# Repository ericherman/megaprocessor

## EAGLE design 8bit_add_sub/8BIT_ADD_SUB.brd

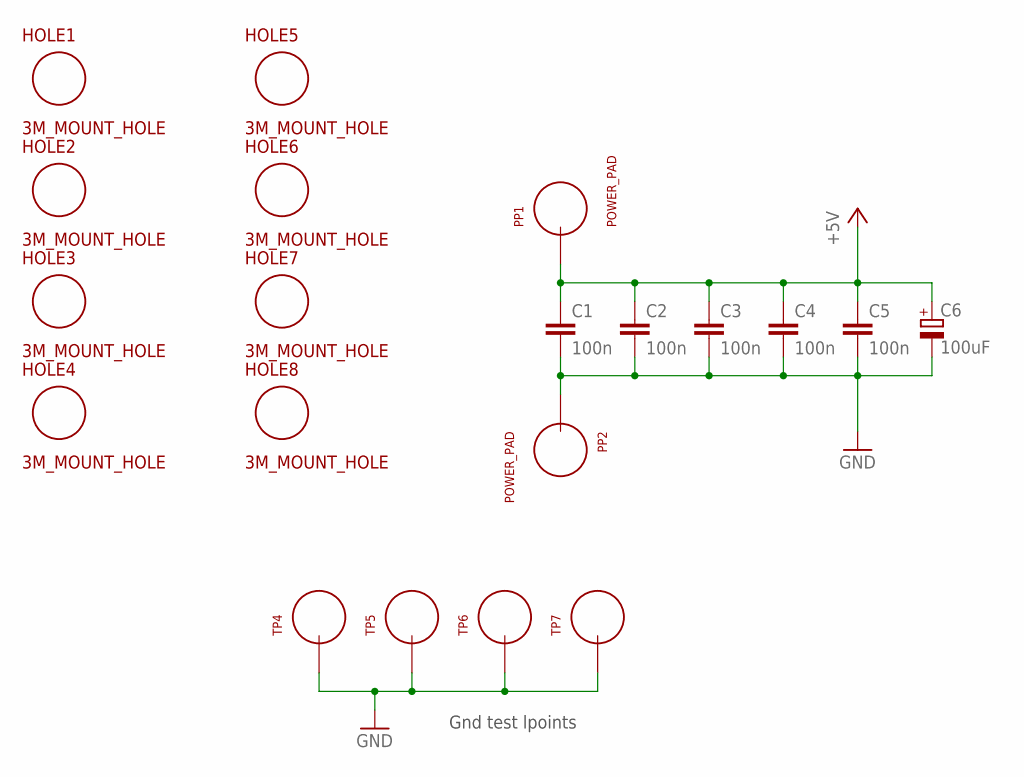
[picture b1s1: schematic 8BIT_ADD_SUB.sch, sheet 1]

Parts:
C1, C2, C3, C4, C5: 100n; CAP_P2INCH
C6: 100uF; POLARISED_CAP_2P5
HOLE1, HOLE2, HOLE3, HOLE4, HOLE5, HOLE6, HOLE7, HOLE8: 3M_MOUNT_HOLE; 3M_HOLE
PP1, PP2: POWER_PAD
TP4, TP5, TP6, TP7: TEST_LOOP

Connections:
+5V: C1.1, C2.1, C3.1, C4.1, C5.1, C6.A, PP1.1; also elsewhere on the board
GND: C1.2, C2.2, C3.2, C4.2, C5.2, C6.K, PP2.1, TP4.P$1, TP5.P$1, TP6.P$1, TP7.P$1; also elsewhere on the board

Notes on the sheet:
Gnd test lpoints

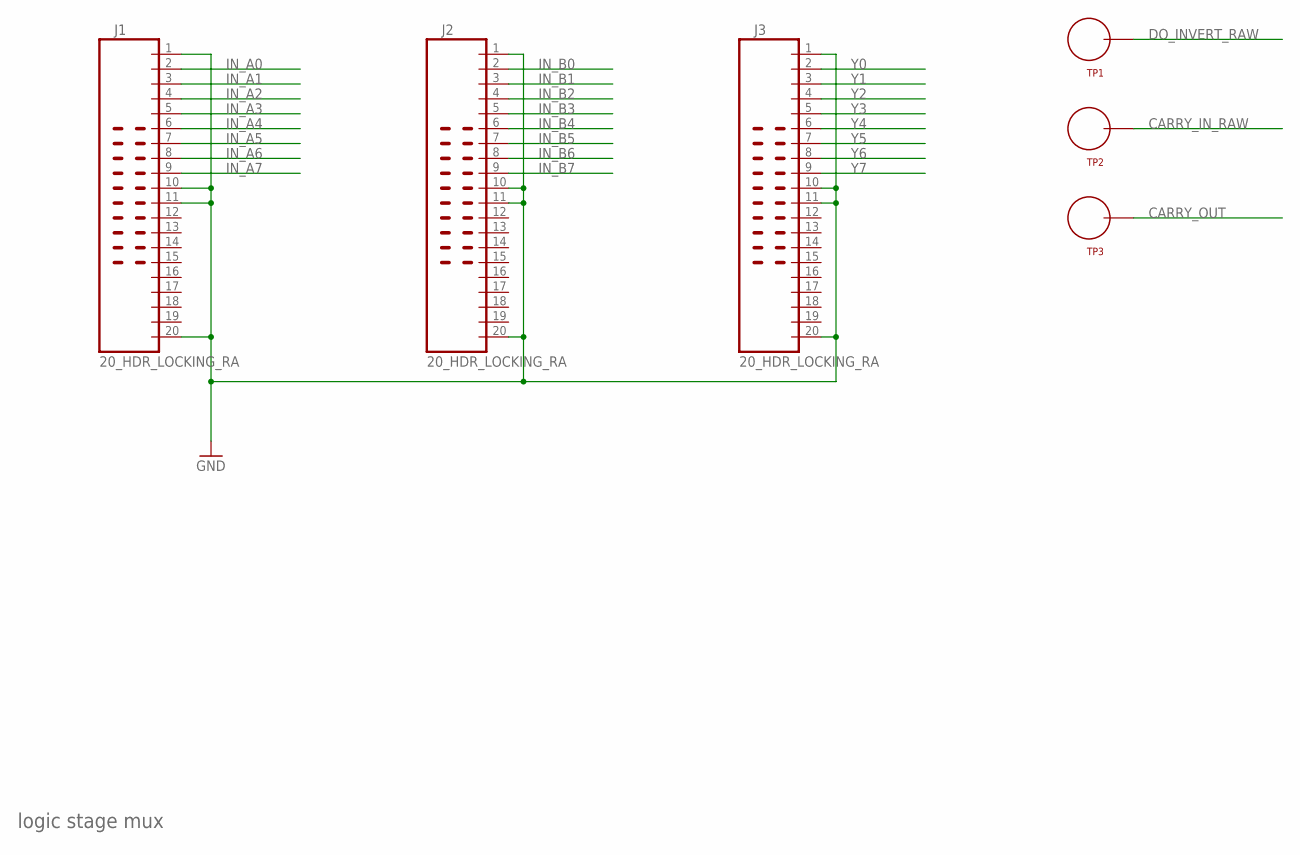
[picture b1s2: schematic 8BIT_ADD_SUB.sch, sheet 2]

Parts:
J1, J2, J3: 20_HDR_LOCKING_RA
TP1, TP2, TP3: TEST_LOOP

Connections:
CARRY_IN_RAW: TP2.P$1; also elsewhere on the board
CARRY_OUT: TP3.P$1; also elsewhere on the board
DO_INVERT_RAW: TP1.P$1; also elsewhere on the board
GND: J1.1, J1.10, J1.11, J1.20, J2.1, J2.10, J2.11, J2.20, J3.1, J3.10, J3.11, J3.20; also elsewhere on the board
IN_A0: J1.2; also elsewhere on the board
IN_A1: J1.3; also elsewhere on the board
IN_A2: J1.4; also elsewhere on the board
IN_A3: J1.5; also elsewhere on the board
IN_A4: J1.6; also elsewhere on the board
IN_A5: J1.7; also elsewhere on the board
IN_A6: J1.8; also elsewhere on the board
IN_A7: J1.9; also elsewhere on the board
IN_B0: J2.2; also elsewhere on the board
IN_B1: J2.3; also elsewhere on the board
IN_B2: J2.4; also elsewhere on the board
IN_B3: J2.5; also elsewhere on the board
IN_B4: J2.6; also elsewhere on the board
IN_B5: J2.7; also elsewhere on the board
IN_B6: J2.8; also elsewhere on the board
IN_B7: J2.9; also elsewhere on the board
Y0: J3.2; also elsewhere on the board
Y1: J3.3; also elsewhere on the board
Y2: J3.4; also elsewhere on the board
Y3: J3.5; also elsewhere on the board
Y4: J3.6; also elsewhere on the board
Y5: J3.7; also elsewhere on the board
Y6: J3.8; also elsewhere on the board
Y7: J3.9; also elsewhere on the board

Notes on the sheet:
logic stage mux

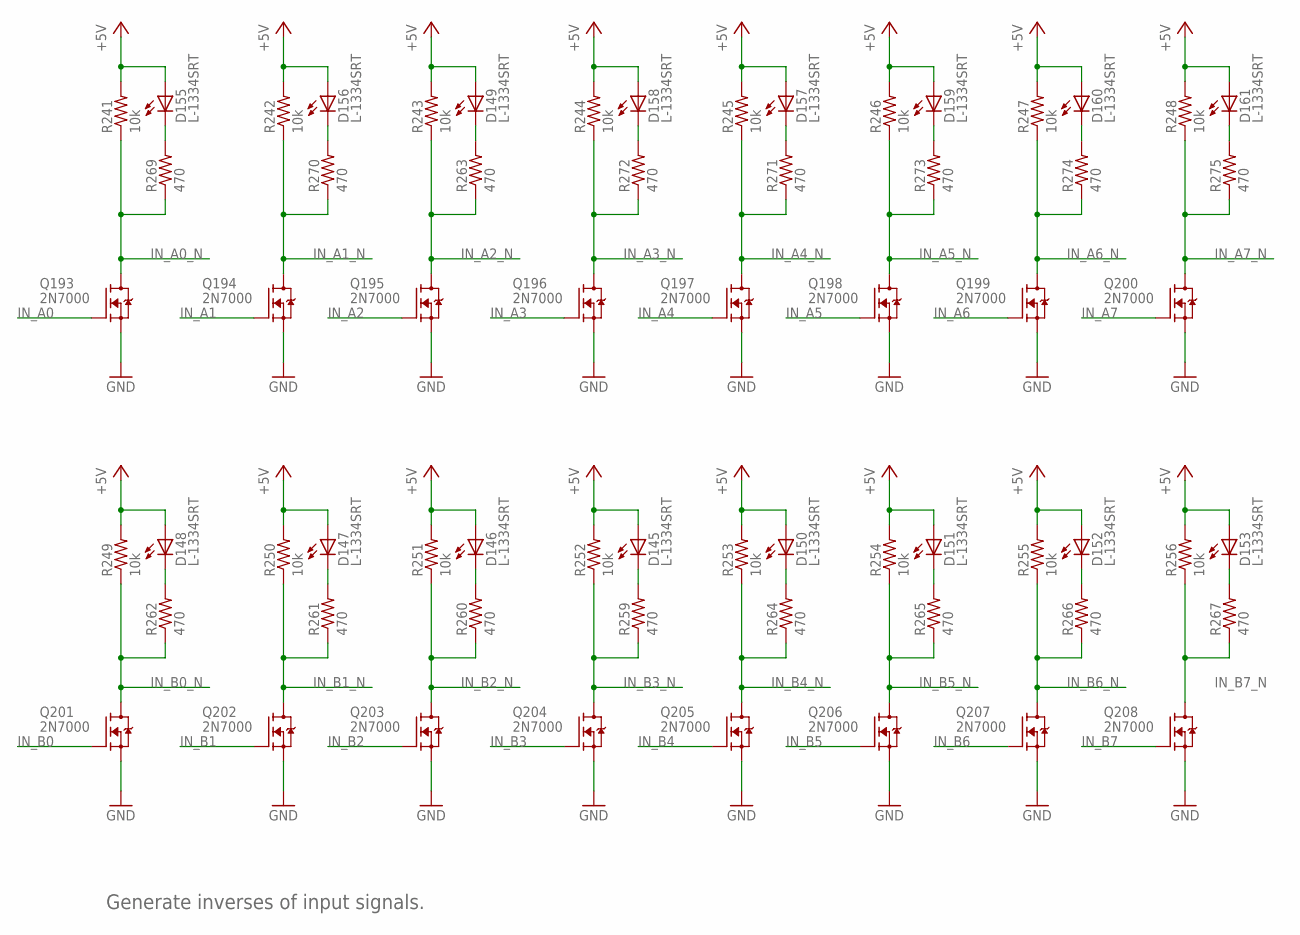
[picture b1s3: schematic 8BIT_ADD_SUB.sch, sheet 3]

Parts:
D145, D146, D147, D148, D149, D150, D151, D152, D153, D155, D156, D157, D158, D159, D160, D161: L-1334SRT; LED3MM
Q193, Q194, Q195, Q196, Q197, Q198, Q199, Q200, Q201, Q202, Q203, Q204, Q205, Q206, Q207, Q208: 2N7000; TO92-DGS
R241, R242, R243, R244, R245, R246, R247, R248, R249, R250, R251, R252, R253, R254, R255, R256: 10k; R_P2INCH
R259, R260, R261, R262, R263, R264, R265, R266, R267, R269, R270, R271, R272, R273, R274, R275: 470; R_P2INCH

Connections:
+5V: D145.A, D146.A, D147.A, D148.A, D149.A, D150.A, D151.A, D152.A, D153.A, D155.A, D156.A, D157.A, D158.A, D159.A, D160.A, D161.A, R241.2, R242.2, R243.2, R244.2, R245.2, R246.2, R247.2, R248.2, R249.2, R250.2, R251.2, R252.2, R253.2, R254.2, R255.2, R256.2; also elsewhere on the board
GND: Q193.S, Q194.S, Q195.S, Q196.S, Q197.S, Q198.S, Q199.S, Q200.S, Q201.S, Q202.S, Q203.S, Q204.S, Q205.S, Q206.S, Q207.S, Q208.S; also elsewhere on the board
IN_A0: Q193.G; also elsewhere on the board
IN_A0_N: Q193.D, R241.1, R269.1; also elsewhere on the board
IN_A1: Q194.G; also elsewhere on the board
IN_A1_N: Q194.D, R242.1, R270.1; also elsewhere on the board
IN_A2: Q195.G; also elsewhere on the board
IN_A2_N: Q195.D, R243.1, R263.1; also elsewhere on the board
IN_A3: Q196.G; also elsewhere on the board
IN_A3_N: Q196.D, R244.1, R272.1; also elsewhere on the board
IN_A4: Q197.G; also elsewhere on the board
IN_A4_N: Q197.D, R245.1, R271.1; also elsewhere on the board
IN_A5: Q198.G; also elsewhere on the board
IN_A5_N: Q198.D, R246.1, R273.1; also elsewhere on the board
IN_A6: Q199.G; also elsewhere on the board
IN_A6_N: Q199.D, R247.1, R274.1; also elsewhere on the board
IN_A7: Q200.G; also elsewhere on the board
IN_A7_N: Q200.D, R248.1, R275.1; also elsewhere on the board
IN_B0: Q201.G; also elsewhere on the board
IN_B0_N: Q201.D, R249.1, R262.1; also elsewhere on the board
IN_B1: Q202.G; also elsewhere on the board
IN_B1_N: Q202.D, R250.1, R261.1; also elsewhere on the board
IN_B2: Q203.G; also elsewhere on the board
IN_B2_N: Q203.D, R251.1, R260.1; also elsewhere on the board
IN_B3: Q204.G; also elsewhere on the board
IN_B3_N: Q204.D, R252.1, R259.1; also elsewhere on the board
IN_B4: Q205.G; also elsewhere on the board
IN_B4_N: Q205.D, R253.1, R264.1; also elsewhere on the board
IN_B5: Q206.G; also elsewhere on the board
IN_B5_N: Q206.D, R254.1, R265.1; also elsewhere on the board
IN_B6: Q207.G; also elsewhere on the board
IN_B6_N: Q207.D, R255.1, R266.1; also elsewhere on the board
IN_B7: Q208.G; also elsewhere on the board
IN_B7_N: Q208.D, R256.1, R267.1; also elsewhere on the board
unnamed: D145.K (C), R259.2
unnamed: D146.K (C), R260.2
unnamed: D147.K (C), R261.2
unnamed: D148.K (C), R262.2
unnamed: D149.K (C), R263.2
unnamed: D150.K (C), R264.2
unnamed: D151.K (C), R265.2
unnamed: D152.K (C), R266.2
unnamed: D153.K (C), R267.2
unnamed: D155.K (C), R269.2
unnamed: D156.K (C), R270.2
unnamed: D157.K (C), R271.2
unnamed: D158.K (C), R272.2
unnamed: D159.K (C), R273.2
unnamed: D160.K (C), R274.2
unnamed: D161.K (C), R275.2

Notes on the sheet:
Generate inverses of input signals.

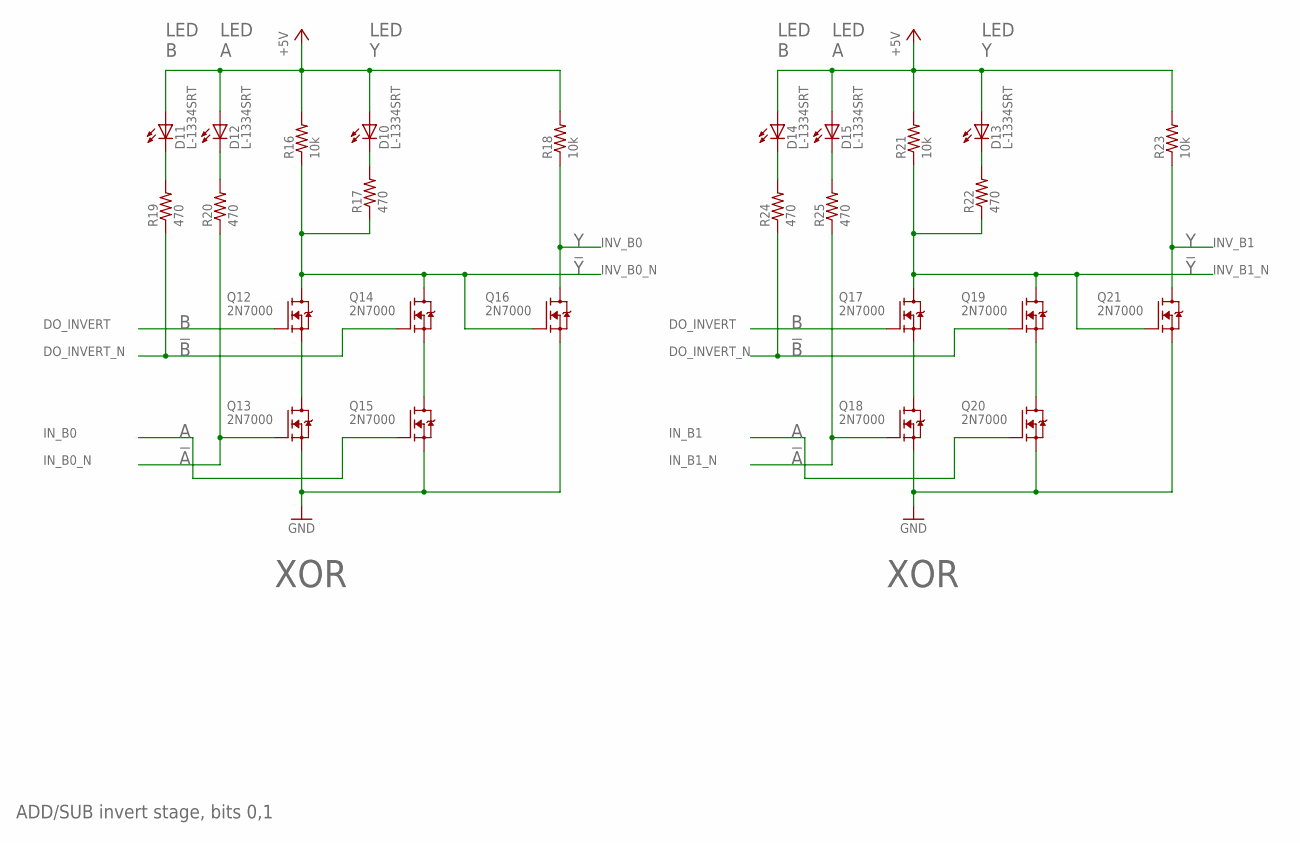
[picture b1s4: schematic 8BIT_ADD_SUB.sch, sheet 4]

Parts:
D10, D11, D12, D13, D14, D15: L-1334SRT; LED3MM
Q12, Q13, Q14, Q15, Q16, Q17, Q18, Q19, Q20, Q21: 2N7000; TO92-DGS
R16, R18, R21, R23: 10k; R_P2INCH
R17, R19, R20, R22, R24, R25: 470; R_P2INCH

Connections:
+5V: D10.A, D11.A, D12.A, D13.A, D14.A, D15.A, R16.2, R18.2, R21.2, R23.2; also elsewhere on the board
DO_INVERT: Q12.G, Q17.G; also elsewhere on the board
DO_INVERT_N: Q14.G, Q19.G, R19.1, R24.1; also elsewhere on the board
GND: Q13.S, Q15.S, Q16.S, Q18.S, Q20.S, Q21.S; also elsewhere on the board
INV_B0: Q16.D, R18.1; also elsewhere on the board
INV_B0_N: Q12.D, Q14.D, Q16.G, R16.1, R17.1; also elsewhere on the board
INV_B1: Q21.D, R23.1; also elsewhere on the board
INV_B1_N: Q17.D, Q19.D, Q21.G, R21.1, R22.1; also elsewhere on the board
IN_B0: Q15.G; also elsewhere on the board
IN_B0_N: Q13.G, R20.1; also elsewhere on the board
IN_B1: Q20.G; also elsewhere on the board
IN_B1_N: Q18.G, R25.1; also elsewhere on the board
unnamed: Q12.S, Q13.D
unnamed: Q14.S, Q15.D
unnamed: D10.K (C), R17.2
unnamed: D12.K (C), R20.2
unnamed: D11.K (C), R19.2
unnamed: Q17.S, Q18.D
unnamed: Q19.S, Q20.D
unnamed: D13.K (C), R22.2
unnamed: D15.K (C), R25.2
unnamed: D14.K (C), R24.2

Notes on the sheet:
ADD/SUB invert stage, bits 0,1
XOR
LED A
LED B
LED Y

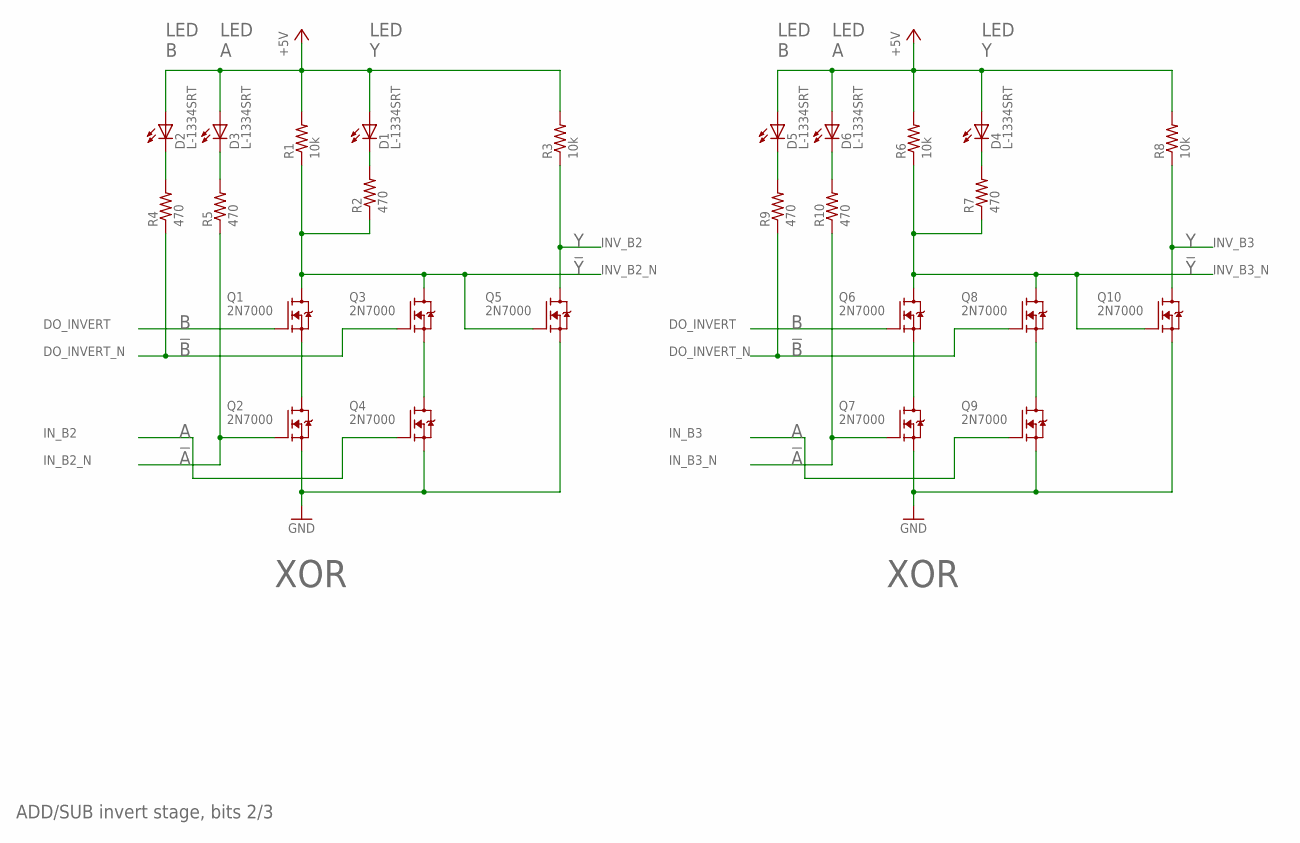
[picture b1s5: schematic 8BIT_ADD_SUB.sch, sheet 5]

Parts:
D1, D2, D3, D4, D5, D6: L-1334SRT; LED3MM
Q1, Q2, Q3, Q4, Q5, Q6, Q7, Q8, Q9, Q10: 2N7000; TO92-DGS
R1, R3, R6, R8: 10k; R_P2INCH
R2, R4, R5, R7, R9, R10: 470; R_P2INCH

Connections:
+5V: D1.A, D2.A, D3.A, D4.A, D5.A, D6.A, R1.2, R3.2, R6.2, R8.2; also elsewhere on the board
DO_INVERT: Q1.G, Q6.G; also elsewhere on the board
DO_INVERT_N: Q3.G, Q8.G, R4.1, R9.1; also elsewhere on the board
GND: Q2.S, Q4.S, Q5.S, Q7.S, Q9.S, Q10.S; also elsewhere on the board
INV_B2: Q5.D, R3.1; also elsewhere on the board
INV_B2_N: Q1.D, Q3.D, Q5.G, R1.1, R2.1; also elsewhere on the board
INV_B3: Q10.D, R8.1; also elsewhere on the board
INV_B3_N: Q6.D, Q8.D, Q10.G, R6.1, R7.1; also elsewhere on the board
IN_B2: Q4.G; also elsewhere on the board
IN_B2_N: Q2.G, R5.1; also elsewhere on the board
IN_B3: Q9.G; also elsewhere on the board
IN_B3_N: Q7.G, R10.1; also elsewhere on the board
unnamed: Q1.S, Q2.D
unnamed: Q3.S, Q4.D
unnamed: D1.K (C), R2.2
unnamed: D3.K (C), R5.2
unnamed: D2.K (C), R4.2
unnamed: Q6.S, Q7.D
unnamed: Q8.S, Q9.D
unnamed: D4.K (C), R7.2
unnamed: D6.K (C), R10.2
unnamed: D5.K (C), R9.2

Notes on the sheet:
ADD/SUB invert stage, bits 2/3
XOR
LED A
LED B
LED Y

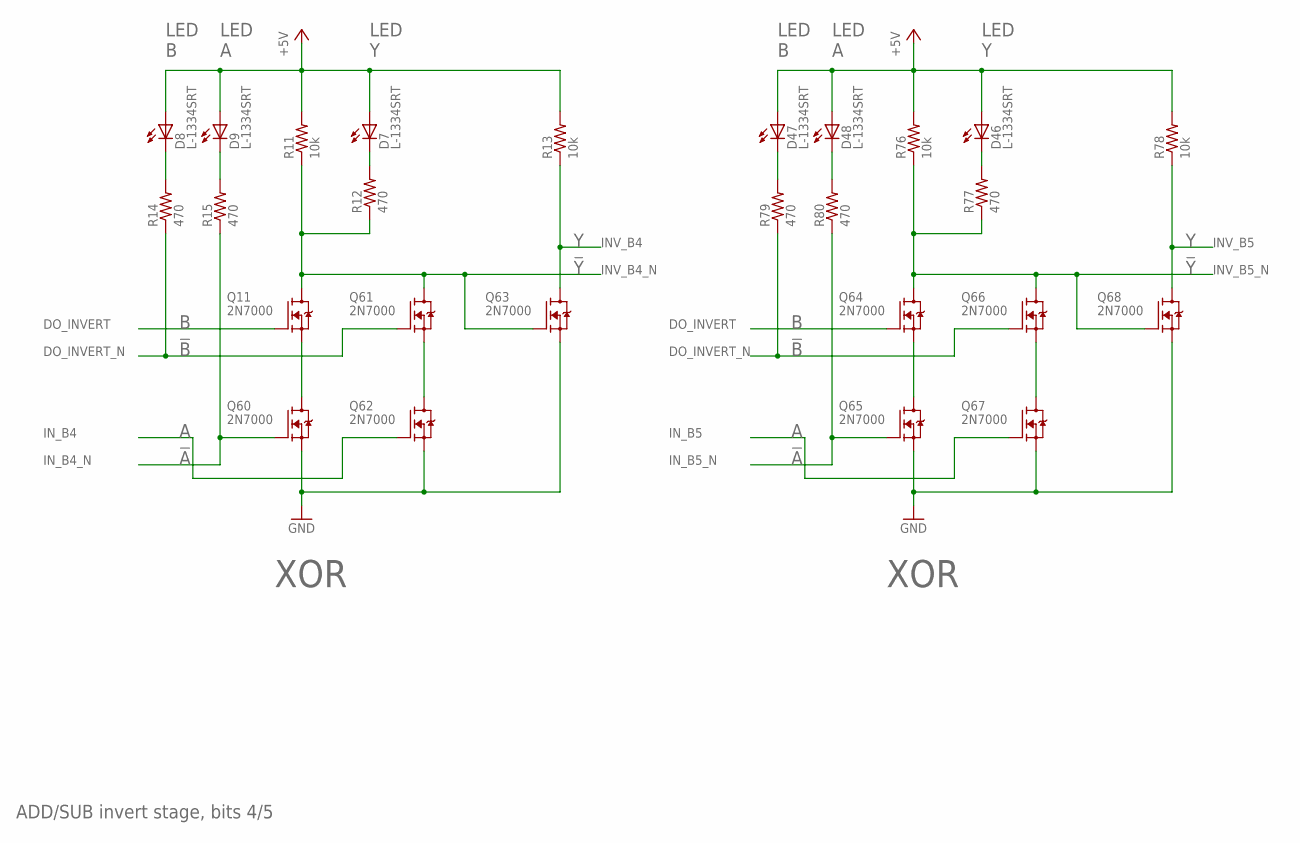
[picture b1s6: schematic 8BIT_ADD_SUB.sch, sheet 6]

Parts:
D7, D8, D9, D46, D47, D48: L-1334SRT; LED3MM
Q11, Q60, Q61, Q62, Q63, Q64, Q65, Q66, Q67, Q68: 2N7000; TO92-DGS
R11, R13, R76, R78: 10k; R_P2INCH
R12, R14, R15, R77, R79, R80: 470; R_P2INCH

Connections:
+5V: D7.A, D8.A, D9.A, D46.A, D47.A, D48.A, R11.2, R13.2, R76.2, R78.2; also elsewhere on the board
DO_INVERT: Q11.G, Q64.G; also elsewhere on the board
DO_INVERT_N: Q61.G, Q66.G, R14.1, R79.1; also elsewhere on the board
GND: Q60.S, Q62.S, Q63.S, Q65.S, Q67.S, Q68.S; also elsewhere on the board
INV_B4: Q63.D, R13.1; also elsewhere on the board
INV_B4_N: Q11.D, Q61.D, Q63.G, R11.1, R12.1; also elsewhere on the board
INV_B5: Q68.D, R78.1; also elsewhere on the board
INV_B5_N: Q64.D, Q66.D, Q68.G, R76.1, R77.1; also elsewhere on the board
IN_B4: Q62.G; also elsewhere on the board
IN_B4_N: Q60.G, R15.1; also elsewhere on the board
IN_B5: Q67.G; also elsewhere on the board
IN_B5_N: Q65.G, R80.1; also elsewhere on the board
unnamed: Q11.S, Q60.D
unnamed: Q61.S, Q62.D
unnamed: D7.K (C), R12.2
unnamed: D9.K (C), R15.2
unnamed: D8.K (C), R14.2
unnamed: Q64.S, Q65.D
unnamed: Q66.S, Q67.D
unnamed: D46.K (C), R77.2
unnamed: D48.K (C), R80.2
unnamed: D47.K (C), R79.2

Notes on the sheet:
ADD/SUB invert stage, bits 4/5
XOR
LED A
LED B
LED Y

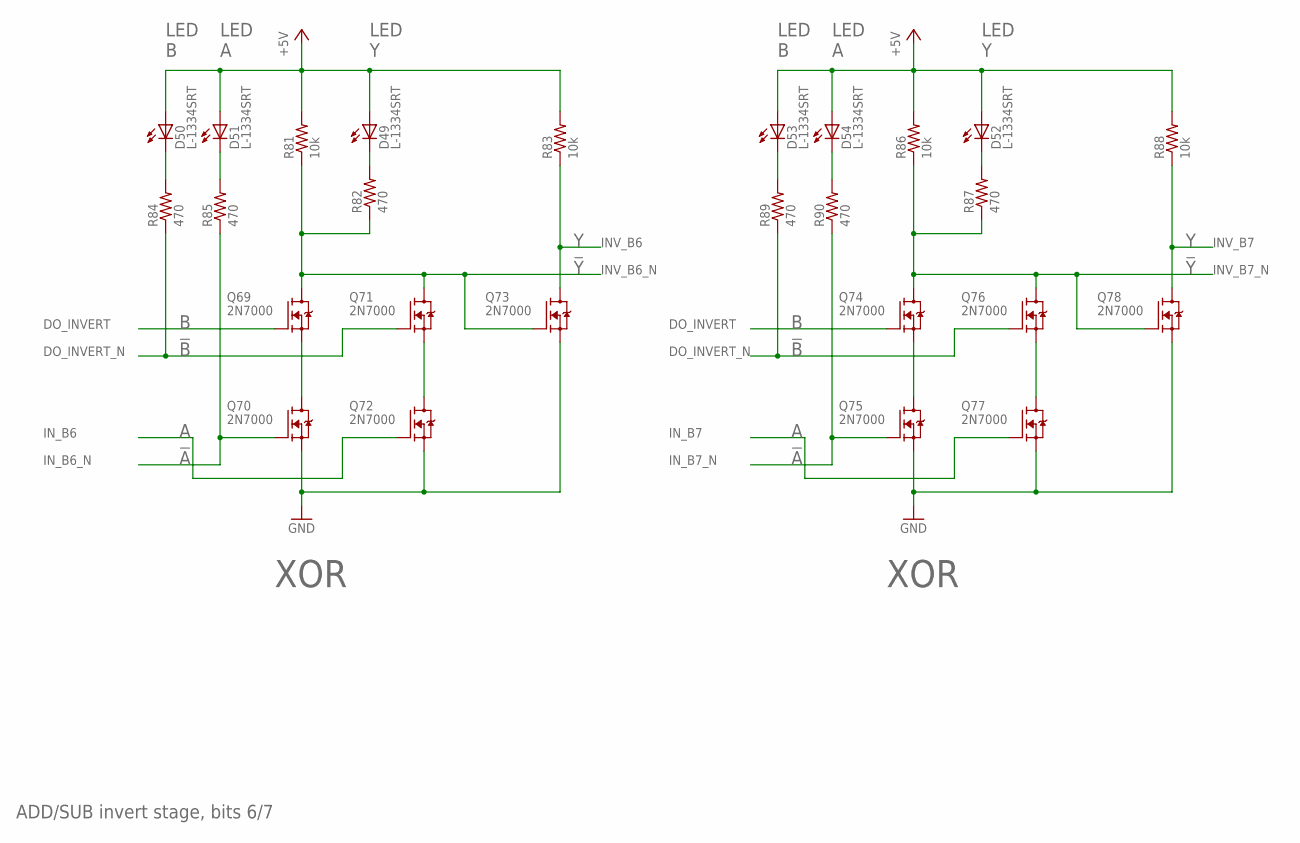
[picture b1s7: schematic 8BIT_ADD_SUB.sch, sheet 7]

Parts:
D49, D50, D51, D52, D53, D54: L-1334SRT; LED3MM
Q69, Q70, Q71, Q72, Q73, Q74, Q75, Q76, Q77, Q78: 2N7000; TO92-DGS
R81, R83, R86, R88: 10k; R_P2INCH
R82, R84, R85, R87, R89, R90: 470; R_P2INCH

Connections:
+5V: D49.A, D50.A, D51.A, D52.A, D53.A, D54.A, R81.2, R83.2, R86.2, R88.2; also elsewhere on the board
DO_INVERT: Q69.G, Q74.G; also elsewhere on the board
DO_INVERT_N: Q71.G, Q76.G, R84.1, R89.1; also elsewhere on the board
GND: Q70.S, Q72.S, Q73.S, Q75.S, Q77.S, Q78.S; also elsewhere on the board
INV_B6: Q73.D, R83.1; also elsewhere on the board
INV_B6_N: Q69.D, Q71.D, Q73.G, R81.1, R82.1; also elsewhere on the board
INV_B7: Q78.D, R88.1; also elsewhere on the board
INV_B7_N: Q74.D, Q76.D, Q78.G, R86.1, R87.1; also elsewhere on the board
IN_B6: Q72.G; also elsewhere on the board
IN_B6_N: Q70.G, R85.1; also elsewhere on the board
IN_B7: Q77.G; also elsewhere on the board
IN_B7_N: Q75.G, R90.1; also elsewhere on the board
unnamed: Q69.S, Q70.D
unnamed: Q71.S, Q72.D
unnamed: D49.K (C), R82.2
unnamed: D51.K (C), R85.2
unnamed: D50.K (C), R84.2
unnamed: Q74.S, Q75.D
unnamed: Q76.S, Q77.D
unnamed: D52.K (C), R87.2
unnamed: D54.K (C), R90.2
unnamed: D53.K (C), R89.2

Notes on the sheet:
ADD/SUB invert stage, bits 6/7
XOR
LED A
LED B
LED Y

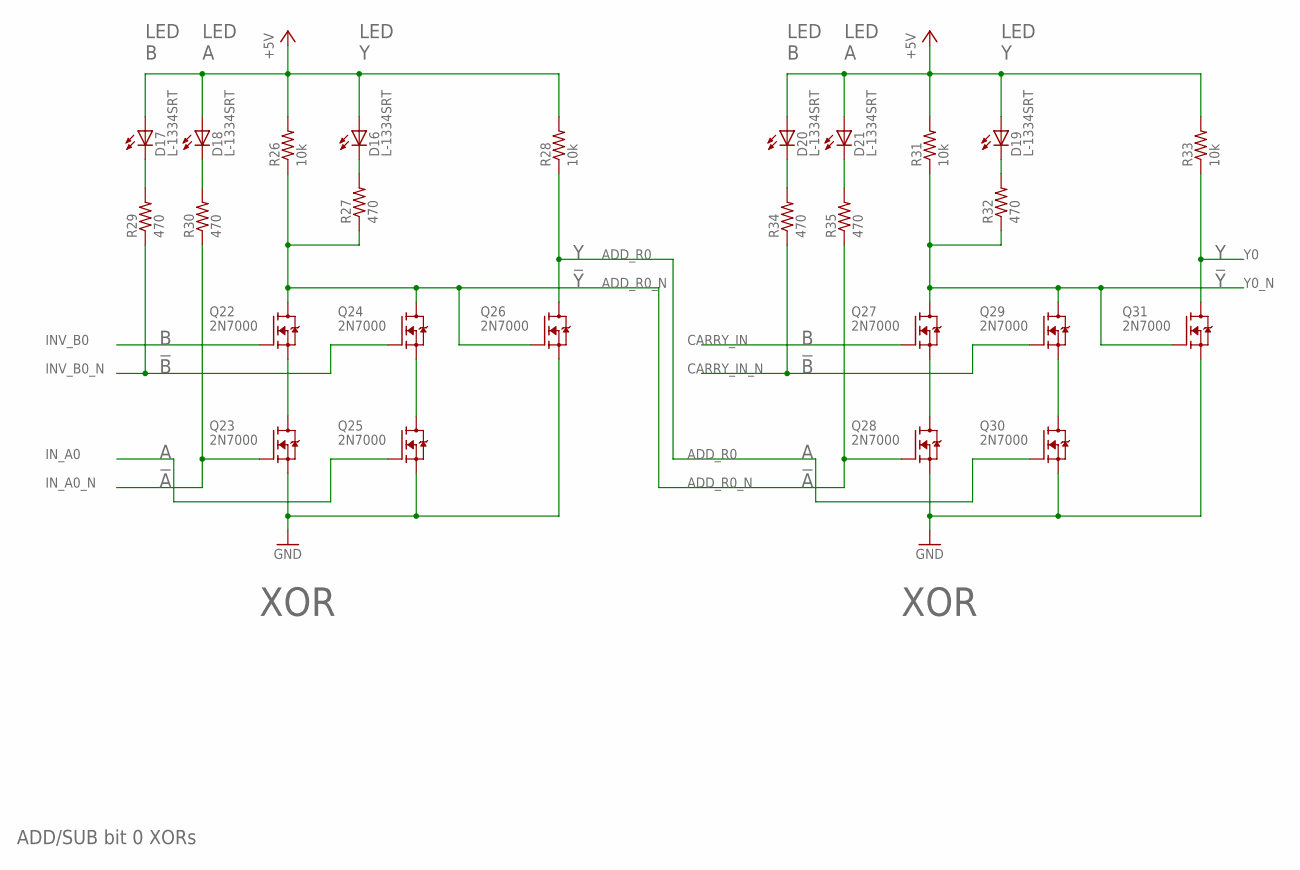
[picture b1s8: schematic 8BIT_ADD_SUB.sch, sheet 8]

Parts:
D16, D17, D18, D19, D20, D21: L-1334SRT; LED3MM
Q22, Q23, Q24, Q25, Q26, Q27, Q28, Q29, Q30, Q31: 2N7000; TO92-DGS
R26, R28, R31, R33: 10k; R_P2INCH
R27, R29, R30, R32, R34, R35: 470; R_P2INCH

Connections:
+5V: D16.A, D17.A, D18.A, D19.A, D20.A, D21.A, R26.2, R28.2, R31.2, R33.2; also elsewhere on the board
ADD_R0: Q26.D, Q30.G, R28.1; also elsewhere on the board
ADD_R0_N: Q22.D, Q24.D, Q26.G, Q28.G, R26.1, R27.1, R35.1; also elsewhere on the board
CARRY_IN: Q27.G; also elsewhere on the board
CARRY_IN_N: Q29.G, R34.1; also elsewhere on the board
GND: Q23.S, Q25.S, Q26.S, Q28.S, Q30.S, Q31.S; also elsewhere on the board
INV_B0: Q22.G; also elsewhere on the board
INV_B0_N: Q24.G, R29.1; also elsewhere on the board
IN_A0: Q25.G; also elsewhere on the board
IN_A0_N: Q23.G, R30.1; also elsewhere on the board
unnamed: Q22.S, Q23.D
unnamed: Q24.S, Q25.D
unnamed: D16.K (C), R27.2
unnamed: D18.K (C), R30.2
unnamed: D17.K (C), R29.2
unnamed: Q27.S, Q28.D
unnamed: Q29.S, Q30.D
unnamed: D19.K (C), R32.2
unnamed: D21.K (C), R35.2
unnamed: D20.K (C), R34.2
Y0: Q31.D, R33.1; also elsewhere on the board
Y0_N: Q27.D, Q29.D, Q31.G, R31.1, R32.1; also elsewhere on the board

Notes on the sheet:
ADD/SUB bit 0 XORs
XOR
LED A
LED B
LED Y

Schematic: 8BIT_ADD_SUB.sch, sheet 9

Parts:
D28, D29, D30, D31, D32, D33, D43, D44, D45: L-1334SRT; LED3MM
Q42, Q43, Q44, Q45, Q46, Q47, Q57, Q58, Q59: 2N7000; TO92-DGS
R46, R48, R51, R53, R71, R73: 10k; R_P2INCH
R47, R49, R50, R52, R54, R55, R72, R74, R75: 470; R_P2INCH

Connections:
+5V: D28.A, D29.A, D30.A, D31.A, D32.A, D33.A, D43.A, D44.A, D45.A, R46.2, R48.2, R51.2, R53.2, R71.2, R73.2; also elsewhere on the board
ADD_R0: Q43.G; also elsewhere on the board
ADD_R0_N: R50.1; also elsewhere on the board
CARRY_IN: Q42.G; also elsewhere on the board
CARRY_IN_N: R49.1; also elsewhere on the board
CGEN_S0: Q44.D, Q45.G, R48.1
CRY0: Q47.D, R53.1; also elsewhere on the board
CRY0_N: Q45.D, Q46.D, Q47.G, R51.1, R52.1; also elsewhere on the board
GND: Q43.S, Q44.S, Q45.S, Q46.S, Q47.S, Q58.S, Q59.S; also elsewhere on the board
INV_B0: Q57.G; also elsewhere on the board
INV_B0_N: R74.1; also elsewhere on the board
IN_A0: Q58.G; also elsewhere on the board
IN_A0_N: R75.1; also elsewhere on the board
unnamed: Q42.S, Q43.D
unnamed: D28.K (C), R47.2
unnamed: Q42.D, Q44.G, R46.1, R47.1, R54.1
unnamed: D30.K (C), R50.2
unnamed: D29.K (C), R49.2
unnamed: D31.K (C), R52.2
unnamed: D33.K (C), R55.2
unnamed: D32.K (C), R54.2
unnamed: Q57.S, Q58.D
unnamed: D43.K (C), R72.2
unnamed: Q46.G, Q59.D, R73.1
unnamed: Q57.D, Q59.G, R55.1, R71.1, R72.1
unnamed: D45.K (C), R75.2
unnamed: D44.K (C), R74.2

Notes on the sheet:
ADD/SUB bit 0 carry generation
AND
LED Y
LED A
LED B

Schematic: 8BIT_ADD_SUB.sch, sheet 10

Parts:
D22, D23, D24, D25, D26, D27: L-1334SRT; LED3MM
Q32, Q33, Q34, Q35, Q36, Q37, Q38, Q39, Q40, Q41: 2N7000; TO92-DGS
R36, R38, R41, R43: 10k; R_P2INCH
R37, R39, R40, R42, R44, R45: 470; R_P2INCH

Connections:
+5V: D22.A, D23.A, D24.A, D25.A, D26.A, D27.A, R36.2, R38.2, R41.2, R43.2; also elsewhere on the board
ADD_R1: Q36.D, Q40.G, R38.1; also elsewhere on the board
ADD_R1_N: Q32.D, Q34.D, Q36.G, Q38.G, R36.1, R37.1, R45.1; also elsewhere on the board
CRY0: Q37.G; also elsewhere on the board
CRY0_N: Q39.G, R44.1; also elsewhere on the board
GND: Q33.S, Q35.S, Q36.S, Q38.S, Q40.S, Q41.S; also elsewhere on the board
INV_B1: Q32.G; also elsewhere on the board
INV_B1_N: Q34.G, R39.1; also elsewhere on the board
IN_A1: Q35.G; also elsewhere on the board
IN_A1_N: Q33.G, R40.1; also elsewhere on the board
unnamed: Q32.S, Q33.D
unnamed: Q34.S, Q35.D
unnamed: D22.K (C), R37.2
unnamed: D24.K (C), R40.2
unnamed: D23.K (C), R39.2
unnamed: Q37.S, Q38.D
unnamed: Q39.S, Q40.D
unnamed: D25.K (C), R42.2
unnamed: D27.K (C), R45.2
unnamed: D26.K (C), R44.2
Y1: Q41.D, R43.1; also elsewhere on the board
Y1_N: Q37.D, Q39.D, Q41.G, R41.1, R42.1; also elsewhere on the board

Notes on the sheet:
ADD/SUB bit 1 XORs.
XOR
LED A
LED B
LED Y

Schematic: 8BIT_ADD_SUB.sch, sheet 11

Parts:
D34, D35, D36, D37, D38, D39, D40, D41, D42: L-1334SRT; LED3MM
Q48, Q49, Q50, Q51, Q52, Q53, Q54, Q55, Q56: 2N7000; TO92-DGS
R56, R58, R61, R63, R66, R68: 10k; R_P2INCH
R57, R59, R60, R62, R64, R65, R67, R69, R70: 470; R_P2INCH

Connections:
+5V: D34.A, D35.A, D36.A, D37.A, D38.A, D39.A, D40.A, D41.A, D42.A, R56.2, R58.2, R61.2, R63.2, R66.2, R68.2; also elsewhere on the board
ADD_R1: Q49.G; also elsewhere on the board
ADD_R1_N: R60.1; also elsewhere on the board
CRY0: Q48.G; also elsewhere on the board
CRY0_N: R59.1; also elsewhere on the board
CRY1: Q53.D, R63.1; also elsewhere on the board
CRY1_N: Q51.D, Q52.D, Q53.G, R61.1, R62.1; also elsewhere on the board
GND: Q49.S, Q50.S, Q51.S, Q52.S, Q53.S, Q55.S, Q56.S; also elsewhere on the board
INV_B1: Q54.G; also elsewhere on the board
INV_B1_N: R69.1; also elsewhere on the board
IN_A1: Q55.G; also elsewhere on the board
IN_A1_N: R70.1; also elsewhere on the board
unnamed: Q48.S, Q49.D
unnamed: D34.K (C), R57.2
unnamed: Q50.D, Q51.G, R58.1
unnamed: Q48.D, Q50.G, R56.1, R57.1, R64.1
unnamed: D36.K (C), R60.2
unnamed: D35.K (C), R59.2
unnamed: D37.K (C), R62.2
unnamed: D39.K (C), R65.2
unnamed: D38.K (C), R64.2
unnamed: Q54.S, Q55.D
unnamed: D40.K (C), R67.2
unnamed: Q52.G, Q56.D, R68.1
unnamed: Q54.D, Q56.G, R65.1, R66.1, R67.1
unnamed: D42.K (C), R70.2
unnamed: D41.K (C), R69.2

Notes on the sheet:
ADD/SUB Bit 1 carry generation
AND
LED Y
LED A
LED B

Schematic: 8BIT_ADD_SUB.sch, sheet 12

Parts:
D55, D56, D57, D58, D59, D60: L-1334SRT; LED3MM
Q79, Q80, Q81, Q82, Q83, Q84, Q85, Q86, Q87, Q88: 2N7000; TO92-DGS
R91, R93, R96, R98: 10k; R_P2INCH
R92, R94, R95, R97, R99, R100: 470; R_P2INCH

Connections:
+5V: D55.A, D56.A, D57.A, D58.A, D59.A, D60.A, R91.2, R93.2, R96.2, R98.2; also elsewhere on the board
ADD_R2: Q83.D, Q87.G, R93.1; also elsewhere on the board
ADD_R2_N: Q79.D, Q81.D, Q83.G, Q85.G, R91.1, R92.1, R100.1; also elsewhere on the board
CRY1: Q84.G; also elsewhere on the board
CRY1_N: Q86.G, R99.1; also elsewhere on the board
GND: Q80.S, Q82.S, Q83.S, Q85.S, Q87.S, Q88.S; also elsewhere on the board
INV_B2: Q79.G; also elsewhere on the board
INV_B2_N: Q81.G, R94.1; also elsewhere on the board
IN_A2: Q82.G; also elsewhere on the board
IN_A2_N: Q80.G, R95.1; also elsewhere on the board
unnamed: Q79.S, Q80.D
unnamed: Q81.S, Q82.D
unnamed: D55.K (C), R92.2
unnamed: D57.K (C), R95.2
unnamed: D56.K (C), R94.2
unnamed: Q84.S, Q85.D
unnamed: Q86.S, Q87.D
unnamed: D58.K (C), R97.2
unnamed: D60.K (C), R100.2
unnamed: D59.K (C), R99.2
Y2: Q88.D, R98.1; also elsewhere on the board
Y2_N: Q84.D, Q86.D, Q88.G, R96.1, R97.1; also elsewhere on the board

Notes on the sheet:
ADD/SUB bit 2 XORs.
XOR
LED A
LED B
LED Y

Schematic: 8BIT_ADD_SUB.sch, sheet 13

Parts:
D91, D92, D93, D94, D95, D96, D97, D98, D99: L-1334SRT; LED3MM
Q139, Q140, Q141, Q142, Q143, Q144, Q145, Q146, Q147: 2N7000; TO92-DGS
R151, R153, R156, R158, R161, R163: 10k; R_P2INCH
R152, R154, R155, R157, R159, R160, R162, R164, R165: 470; R_P2INCH

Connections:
+5V: D91.A, D92.A, D93.A, D94.A, D95.A, D96.A, D97.A, D98.A, D99.A, R151.2, R153.2, R156.2, R158.2, R161.2, R163.2; also elsewhere on the board
ADD_R2: Q140.G; also elsewhere on the board
ADD_R2_N: R155.1; also elsewhere on the board
CRY1: Q139.G; also elsewhere on the board
CRY1_N: R154.1; also elsewhere on the board
CRY2: Q144.D, R158.1; also elsewhere on the board
CRY2_N: Q142.D, Q143.D, Q144.G, R156.1, R157.1; also elsewhere on the board
GND: Q140.S, Q141.S, Q142.S, Q143.S, Q144.S, Q146.S, Q147.S; also elsewhere on the board
INV_B2: Q145.G; also elsewhere on the board
INV_B2_N: R164.1; also elsewhere on the board
IN_A2: Q146.G; also elsewhere on the board
IN_A2_N: R165.1; also elsewhere on the board
unnamed: Q139.S, Q140.D
unnamed: D91.K (C), R152.2
unnamed: Q141.D, Q142.G, R153.1
unnamed: Q139.D, Q141.G, R151.1, R152.1, R159.1
unnamed: D93.K (C), R155.2
unnamed: D92.K (C), R154.2
unnamed: D94.K (C), R157.2
unnamed: D96.K (C), R160.2
unnamed: D95.K (C), R159.2
unnamed: Q145.S, Q146.D
unnamed: D97.K (C), R162.2
unnamed: Q143.G, Q147.D, R163.1
unnamed: Q145.D, Q147.G, R160.1, R161.1, R162.1
unnamed: D99.K (C), R165.2
unnamed: D98.K (C), R164.2

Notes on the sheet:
ADD/SUB Bit 2 carry generation
AND
LED Y
LED A
LED B

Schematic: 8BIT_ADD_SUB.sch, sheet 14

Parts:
D61, D62, D63, D64, D65, D66: L-1334SRT; LED3MM
Q89, Q90, Q91, Q92, Q93, Q94, Q95, Q96, Q97, Q98: 2N7000; TO92-DGS
R101, R103, R106, R108: 10k; R_P2INCH
R102, R104, R105, R107, R109, R110: 470; R_P2INCH

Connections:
+5V: D61.A, D62.A, D63.A, D64.A, D65.A, D66.A, R101.2, R103.2, R106.2, R108.2; also elsewhere on the board
ADD_R3: Q93.D, Q97.G, R103.1; also elsewhere on the board
ADD_R3_N: Q89.D, Q91.D, Q93.G, Q95.G, R101.1, R102.1, R110.1; also elsewhere on the board
CRY2: Q94.G; also elsewhere on the board
CRY2_N: Q96.G, R109.1; also elsewhere on the board
GND: Q90.S, Q92.S, Q93.S, Q95.S, Q97.S, Q98.S; also elsewhere on the board
INV_B3: Q89.G; also elsewhere on the board
INV_B3_N: Q91.G, R104.1; also elsewhere on the board
IN_A3: Q92.G; also elsewhere on the board
IN_A3_N: Q90.G, R105.1; also elsewhere on the board
unnamed: Q89.S, Q90.D
unnamed: Q91.S, Q92.D
unnamed: D61.K (C), R102.2
unnamed: D63.K (C), R105.2
unnamed: D62.K (C), R104.2
unnamed: Q94.S, Q95.D
unnamed: Q96.S, Q97.D
unnamed: D64.K (C), R107.2
unnamed: D66.K (C), R110.2
unnamed: D65.K (C), R109.2
Y3: Q98.D, R108.1; also elsewhere on the board
Y3_N: Q94.D, Q96.D, Q98.G, R106.1, R107.1; also elsewhere on the board

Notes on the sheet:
ADD/SUB bit 3 XORs.
XOR
LED A
LED B
LED Y

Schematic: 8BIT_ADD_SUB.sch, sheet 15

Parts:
D100, D101, D102, D103, D104, D105, D106, D107, D108: L-1334SRT; LED3MM
Q148, Q149, Q150, Q151, Q152, Q153, Q154, Q155, Q156: 2N7000; TO92-DGS
R166, R168, R171, R173, R176, R178: 10k; R_P2INCH
R167, R169, R170, R172, R174, R175, R177, R179, R180: 470; R_P2INCH

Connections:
+5V: D100.A, D101.A, D102.A, D103.A, D104.A, D105.A, D106.A, D107.A, D108.A, R166.2, R168.2, R171.2, R173.2, R176.2, R178.2; also elsewhere on the board
ADD_R3: Q149.G; also elsewhere on the board
ADD_R3_N: R170.1; also elsewhere on the board
CRY2: Q148.G; also elsewhere on the board
CRY2_N: R169.1; also elsewhere on the board
CRY3: Q153.D, R173.1; also elsewhere on the board
CRY3_N: Q151.D, Q152.D, Q153.G, R171.1, R172.1; also elsewhere on the board
GND: Q149.S, Q150.S, Q151.S, Q152.S, Q153.S, Q155.S, Q156.S; also elsewhere on the board
INV_B3: Q154.G; also elsewhere on the board
INV_B3_N: R179.1; also elsewhere on the board
IN_A3: Q155.G; also elsewhere on the board
IN_A3_N: R180.1; also elsewhere on the board
unnamed: Q148.S, Q149.D
unnamed: D100.K (C), R167.2
unnamed: Q150.D, Q151.G, R168.1
unnamed: Q148.D, Q150.G, R166.1, R167.1, R174.1
unnamed: D102.K (C), R170.2
unnamed: D101.K (C), R169.2
unnamed: D103.K (C), R172.2
unnamed: D105.K (C), R175.2
unnamed: D104.K (C), R174.2
unnamed: Q154.S, Q155.D
unnamed: D106.K (C), R177.2
unnamed: Q152.G, Q156.D, R178.1
unnamed: Q154.D, Q156.G, R175.1, R176.1, R177.1
unnamed: D108.K (C), R180.2
unnamed: D107.K (C), R179.2

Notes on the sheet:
ADD/SUB Bit 3 carry generation
AND
LED Y
LED A
LED B

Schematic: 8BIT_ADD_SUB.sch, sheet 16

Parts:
D67, D68, D69, D70, D71, D72: L-1334SRT; LED3MM
Q99, Q100, Q101, Q102, Q103, Q104, Q105, Q106, Q107, Q108: 2N7000; TO92-DGS
R111, R113, R116, R118: 10k; R_P2INCH
R112, R114, R115, R117, R119, R120: 470; R_P2INCH

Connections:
+5V: D67.A, D68.A, D69.A, D70.A, D71.A, D72.A, R111.2, R113.2, R116.2, R118.2; also elsewhere on the board
ADD_R4: Q103.D, Q107.G, R113.1; also elsewhere on the board
ADD_R4_N: Q99.D, Q101.D, Q103.G, Q105.G, R111.1, R112.1, R120.1; also elsewhere on the board
CRY3: Q104.G; also elsewhere on the board
CRY3_N: Q106.G, R119.1; also elsewhere on the board
GND: Q100.S, Q102.S, Q103.S, Q105.S, Q107.S, Q108.S; also elsewhere on the board
INV_B4: Q99.G; also elsewhere on the board
INV_B4_N: Q101.G, R114.1; also elsewhere on the board
IN_A4: Q102.G; also elsewhere on the board
IN_A4_N: Q100.G, R115.1; also elsewhere on the board
unnamed: Q99.S, Q100.D
unnamed: Q101.S, Q102.D
unnamed: D67.K (C), R112.2
unnamed: D69.K (C), R115.2
unnamed: D68.K (C), R114.2
unnamed: Q104.S, Q105.D
unnamed: Q106.S, Q107.D
unnamed: D70.K (C), R117.2
unnamed: D72.K (C), R120.2
unnamed: D71.K (C), R119.2
Y4: Q108.D, R118.1; also elsewhere on the board
Y4_N: Q104.D, Q106.D, Q108.G, R116.1, R117.1; also elsewhere on the board

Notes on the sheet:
ADD/SUB bit 4 XORs.
XOR
LED A
LED B
LED Y
